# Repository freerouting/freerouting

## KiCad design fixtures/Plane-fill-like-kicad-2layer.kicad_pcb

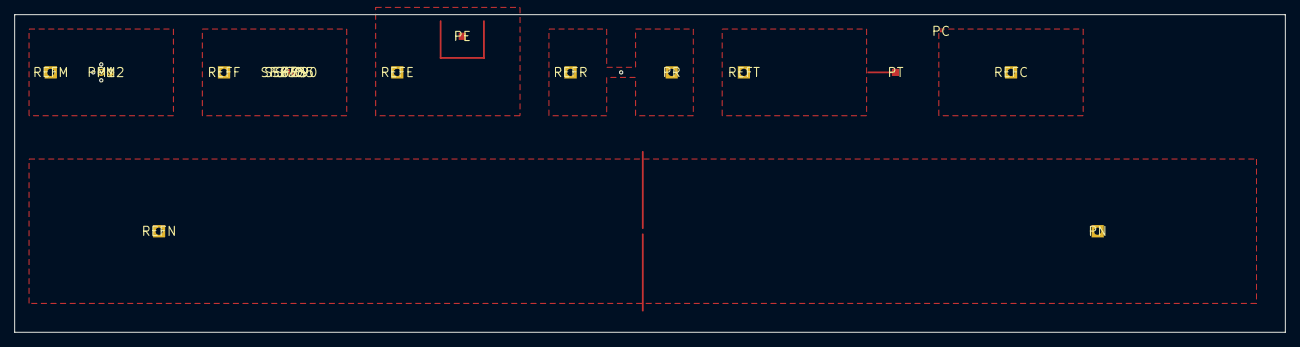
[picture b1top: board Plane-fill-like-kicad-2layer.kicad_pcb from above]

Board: 2 copper layers, 176.0 x 44.0 mm, 19 parts (0 on the bottom side), 8 nets.

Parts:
PC: (no value)
PE: (no value)
PF: (no value)
PM1, PM2: (no value)
PN: (no value)
PR: (no value)
PT: (no value)
REFC: (no value)
REFE: (no value)
REFF: (no value)
REFM: (no value)
REFN: (no value)
REFR: (no value)
REFT: (no value)
SF370, SF375, SF385, SF390: (no value)

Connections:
CRN: PC.1, REFC.1
EDGE: PE.1, REFE.1
FINE: PF.1, REFF.1
MUT: PM1.1, PM2.1, REFM.1
NECK: PN.1, REFN.1
RIM: PR.1, REFR.1
SIG: SF370.1, SF375.1, SF385.1, SF390.1
TRK: PT.1, REFT.1

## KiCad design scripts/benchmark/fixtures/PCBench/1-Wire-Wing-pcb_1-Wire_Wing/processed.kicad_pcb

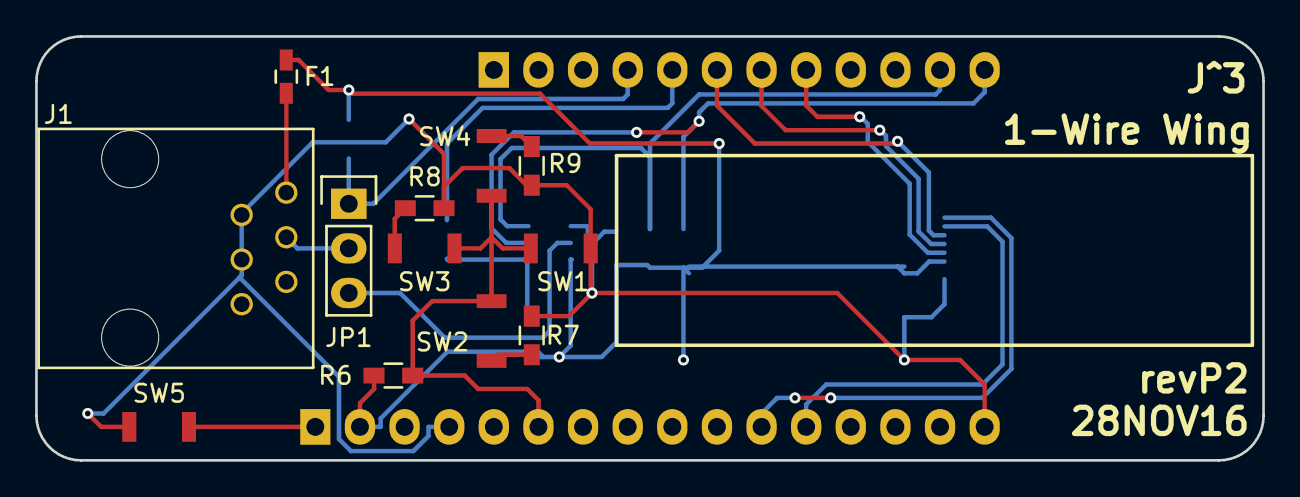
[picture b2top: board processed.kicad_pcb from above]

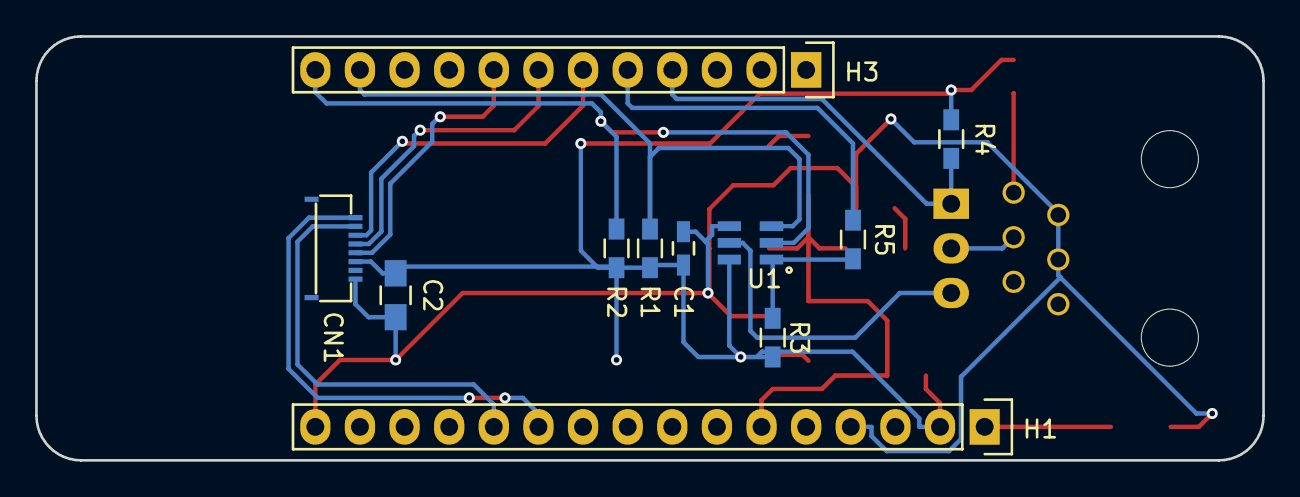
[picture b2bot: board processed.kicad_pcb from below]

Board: 2 copper layers, 69.9 x 24.1 mm, 23 parts (11 on the bottom side), 20 nets.

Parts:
C1: 0.1uF; C_0603_HandSoldering
C2: 2uF; C_0805_HandSoldering
CN1: CONN_01X08; HIROSE_FH19C-8S-0.5SH(05)
F1: FUSE; C_0603_HandSoldering
H1: CONN_01X16; Pin_Header_Straight_1x16
H3: CONN_01X12; Pin_Header_Straight_1x12
J1: RJ11; TE_6P6C_5555165-1
JP1: CONN_01X03; Pin_Header_Straight_1x03
R1, R2, R7: 3.3K; R_0603_HandSoldering
R3: 2.2K; R_0603_HandSoldering
R4: 1K; R_0603_HandSoldering
R5: DNI; R_0603_HandSoldering
R6, R8: 10K; R_0603_HandSoldering
R9: 33K; R_0603_HandSoldering
SW1, SW2, SW3, SW4, SW5: SW_PUSH_SMALL_H; OMRON_B3U-1000P
U1: DS2484R+; SOT95P280X125-6N

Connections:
+3V3: C1.1, C2.1, CN1.6, F1.1, H1.2, R1.1, R2.1, R3.1, R4.1, R6.1, U1.6
/1-Wire: J1.3, JP1.2
/CS: CN1.3, H3.6
/DISP: CN1.5, H3.8
/EXTCOMIN: CN1.4, H3.7
/MOSI: CN1.2, H1.12
/OWM: H3.4, JP1.1, R4.2
/SCL: H3.11, R1.2, U1.3
/SCLK: CN1.1, H1.11
/SDA: H3.12, R2.2, U1.2
/~RESET: H1.1, SW5.1
/~SLPZ: H3.5, R5.2
GND: C1.2, C2.2, CN1.8, H1.4, H1.16, J1.2, J1.4, R7.2, R8.2, R9.2, SW1.1, SW5.2, U1.4
unnamed: F1.2, J1.1
unnamed: H1.6, R6.2, SW1.2, SW2.2, SW3.2, SW4.2
unnamed: JP1.3, U1.5
unnamed: R3.2, R5.1, U1.1
unnamed: R7.1, SW2.1
unnamed: R8.1, SW3.1
unnamed: R9.1, SW4.1
